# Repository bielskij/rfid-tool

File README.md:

An universal USB 125kHz token reader and programmer.

It uses a small Chinese attiny85 based board (adadfruit clone) and a simple custom shiled containing analog demodulator circuit. The shield is not required, whole circuit could be 
assembled on breadboard, but keep in mind that this solution is much more sensitive to noise and glitches.

Current software supports:
 - reading EM4100 RFID tokens
    - 16, 32, 64 carrier divider (auto detection)
    - Manchaster, Biphase data encoding
 - programming T5557 based RFID tokens
Current software allows to:

The following features are scheduled for future development:
- support for PSK encoding,
- password protection and locking (T5557),
- one-shot command to clone a token.

#### Attiny board preparation.

**!! IMPORTANT !!** Reset pin fuse should be disabled. Please keep in mind that it will disable ISP programming permanently, HV programmer is require to restore default setting.

The chinese PCB has a micronucleus bootloader preinstalled. It is sufficient to upgrade firmware in the attiny trough USB. No other modifications are required. The project has no micronucleus commandline utility included. Manual installation from package repository or source code is required [(link)](https://github.com/micronucleus/micronucleus).

The following command will compile and burn firmware in attiny:

```console
# cd firmware
# make clean all burn
```

#### Host software compilation.

Host software depends on libusb library. It was tested on a linux system (Ubuntu) only.

```console
# cd rfid-tool
# make clean all
```

#### Basic use cases.

```console
---- Reading a EM4100 token

# ./out/rfid-tool -r
New token, carrier divider: 64, modulation: Manchester, customer ID: 75 (0x4b), token: 1469220 (0x166b24)
New token, carrier divider: 64, modulation: Manchester, customer ID: 75 (0x4b), token: 1469220 (0x166b24)

---- Programming a T5557 token

# ./out/rfid-tool -p -b 64 -m manchester -c 0x4b -t 0x166b24

---- Reset to bootloader (firmware upgrade)

# ./out/rfid-tool -R
```

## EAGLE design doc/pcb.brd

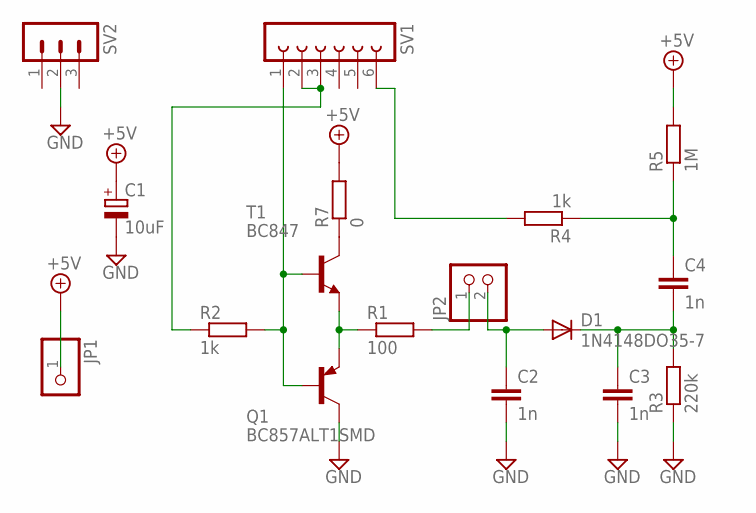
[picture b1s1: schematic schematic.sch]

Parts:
C1: 10uF; E2,5-6
C2, C3, C4: 1n; C050-024X044
D1: 1N4148DO35-7; DO35-7
JP1: PINHD-1X1; 1X01
JP2: PINHD-1X2; 1X02
Q1: BC857ALT1SMD; SOT23-BEC
R1: 100; 0207/10
R2, R4: 1k; 0207/10
R3: 220k; 0207/10
R5: 1M; 0207/10
R7: 0; 0204/5
SV1: FE06-1; FE06
SV2: MA03-1
T1: BC847; SOT23

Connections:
+5V: C1.+, JP1.1, R5.2, R7.2
GND: C1.-, C2.2, C3.2, Q1.C, R3.1, SV2.2
unnamed: Q1.E, R1.1, T1.2 (E)
unnamed: Q1.B, R2.2, SV1.1, T1.1 (B)
unnamed: JP2.1, R1.2
unnamed: C2.1, D1.A, JP2.2
unnamed: C3.1, C4.2, D1.C, R3.2
unnamed: C4.1, R4.1, R5.1
unnamed: R4.2, SV1.6
unnamed: R7.1, T1.3 (C)
unnamed: R2.1, SV1.2, SV1.3

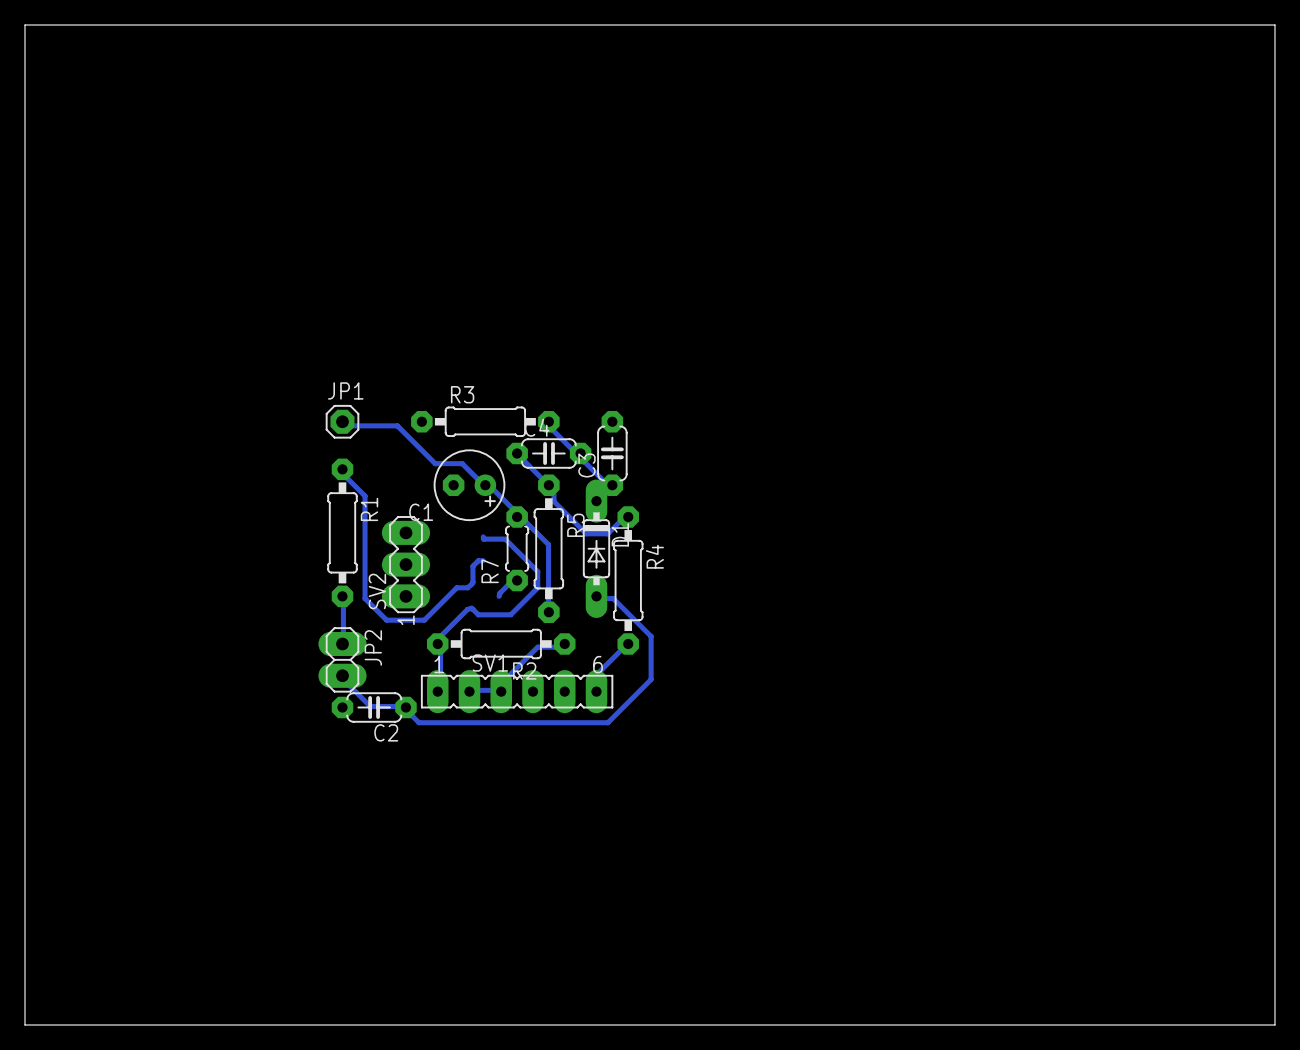
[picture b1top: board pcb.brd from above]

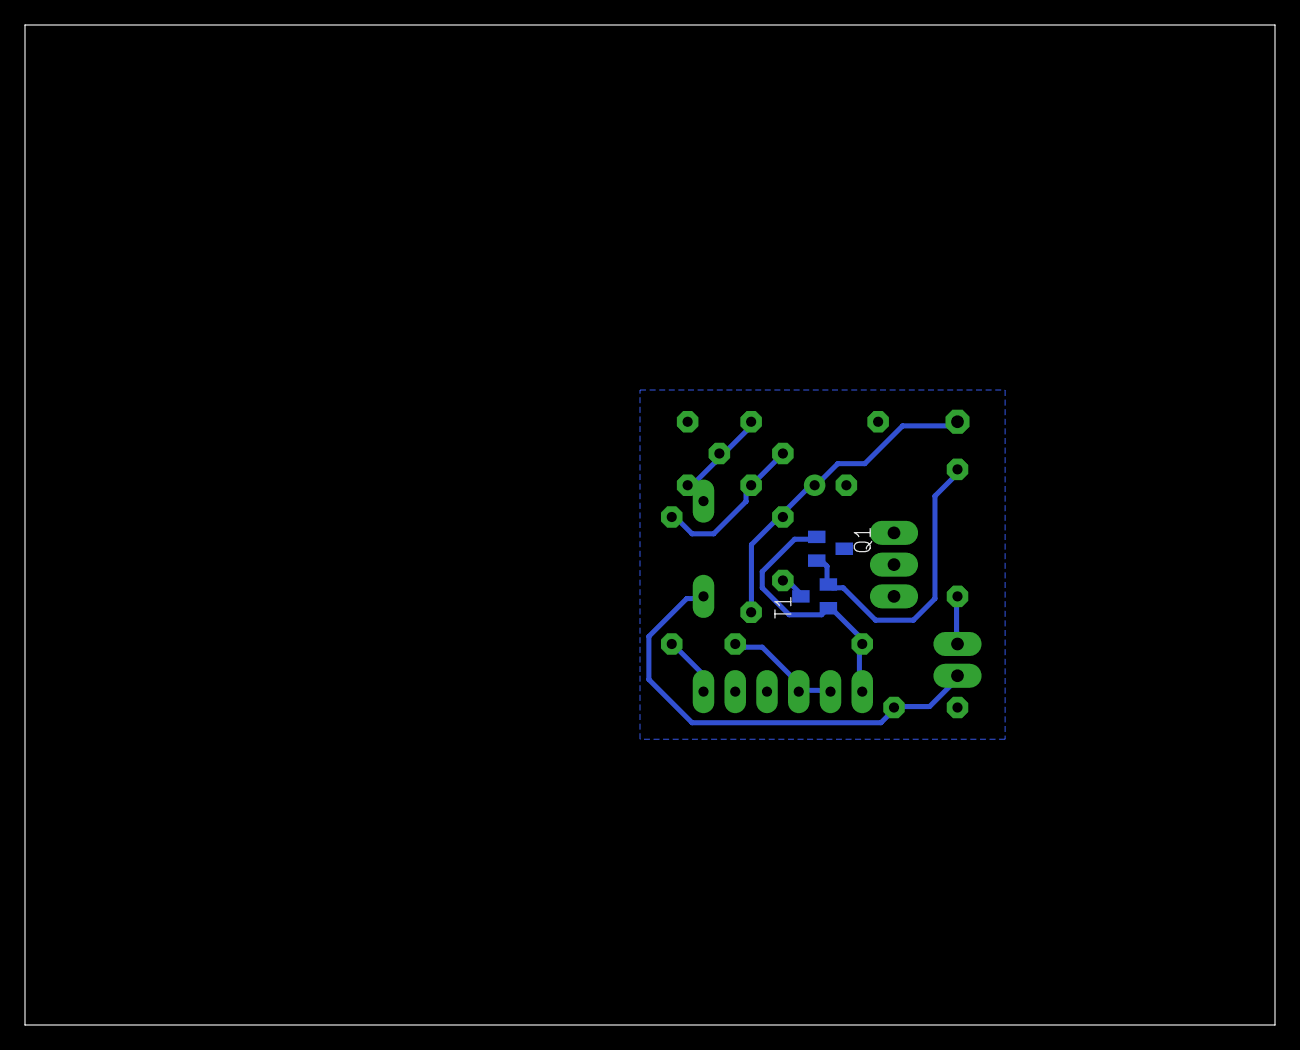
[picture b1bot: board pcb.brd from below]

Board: 2 copper layers, 100.0 x 80.0 mm, 17 parts (2 on the bottom side), 11 nets.

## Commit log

2019-01-06 Added missing common code
2021-02-10 Added biphase encoding support in programming mode
2021-02-10 Fixed invalid biphase variant
2021-02-10 Increase correct pulse length range
2021-02-10 Added Biphase modulation decoder Updated help message
2021-02-10 Updated README file
2022-07-19 Added transfer() method for coil controlling
2022-07-20 Minor fixes
2022-07-21 Transmit operation is now blocking
2022-07-22 Fixed stack overflow in firmware. Fixed some warnings reported by valgrind
